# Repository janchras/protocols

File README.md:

Protocols of 4th year in HTL Kaindorf

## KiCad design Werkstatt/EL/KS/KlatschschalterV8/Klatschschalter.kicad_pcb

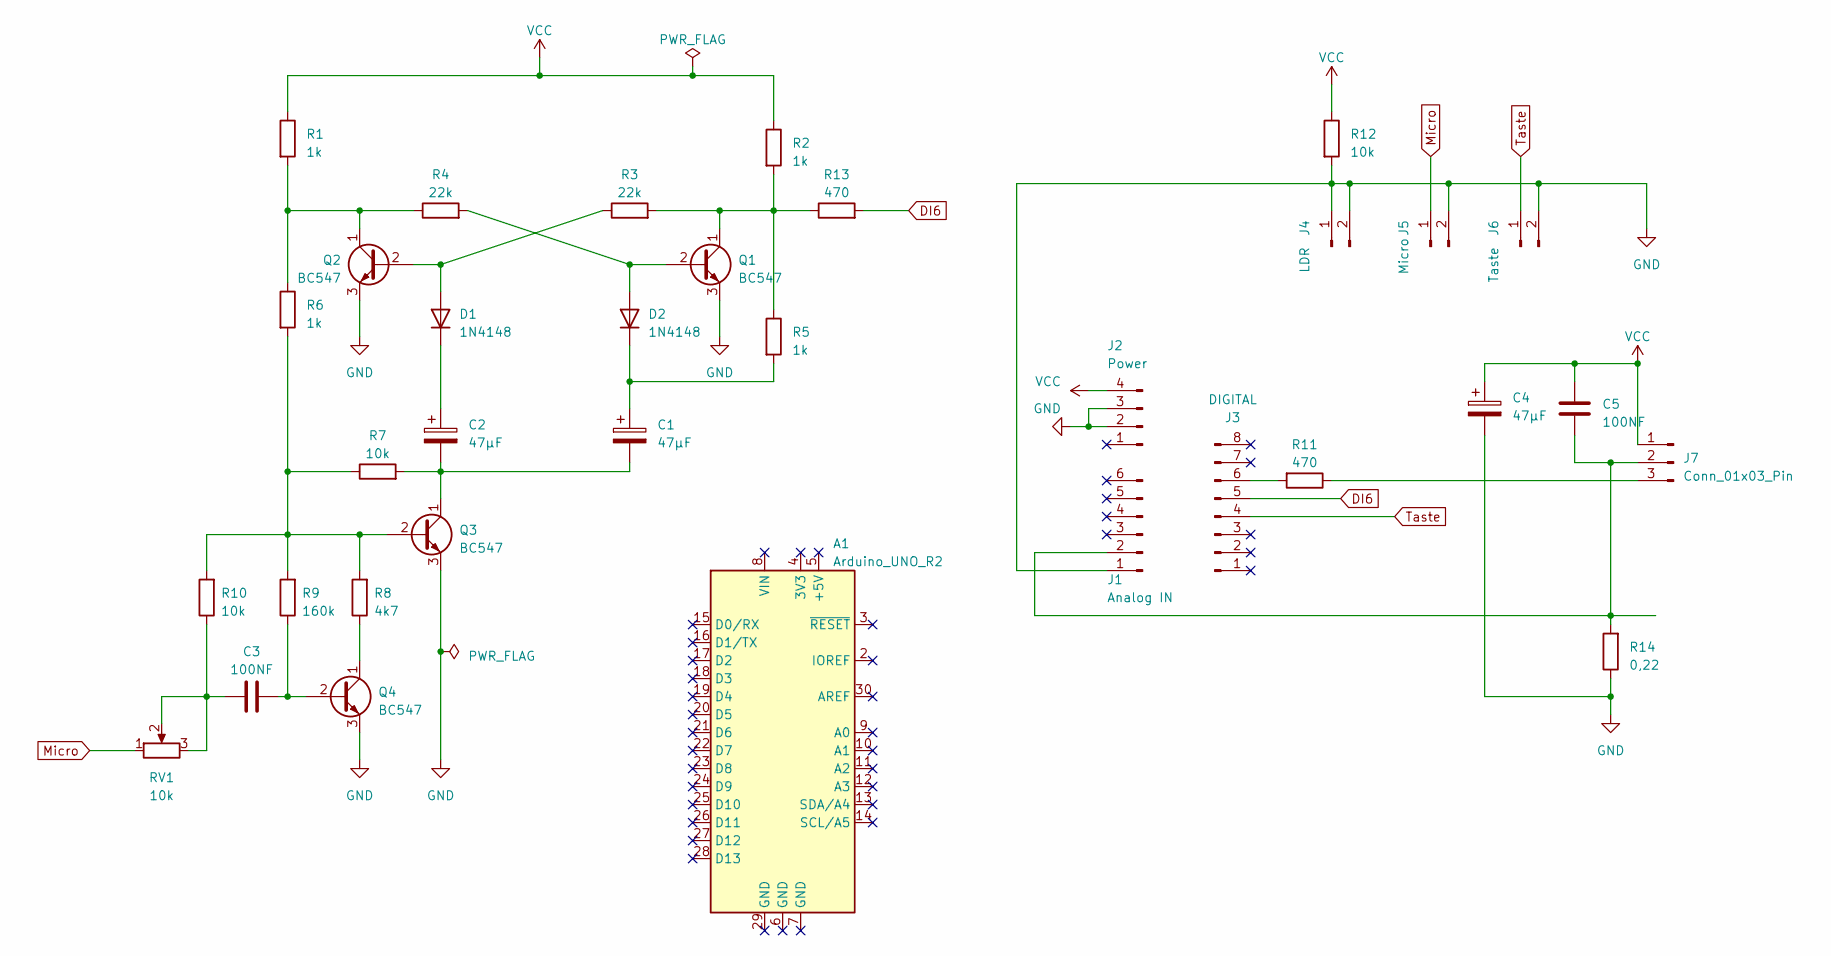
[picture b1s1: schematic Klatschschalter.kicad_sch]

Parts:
A1: Arduino_UNO_R2
C1, C2, C4: 47μF; CP_Radial_D5.0mm_P2.50mm
C3, C5: 100NF; C_Disc_D7.0mm_W2.5mm_P5.00mm
D1, D2: 1N4148; D_DO-35_SOD27_P7.62mm_Horizontal
J1: Analog IN; PinHeader_1x06_P2.54mm_Vertical
J2: Power; PinHeader_1x04_P2.54mm_Vertical
J3: DIGITAL; PinHeader_1x08_P2.54mm_Vertical
J4: LDR; PinHeader_1x02_P2.54mm_Vertical
J5: Micro; PinHeader_1x02_P2.54mm_Vertical
J6: Taste; PinHeader_1x02_P2.54mm_Vertical
J7: Conn_01x03_Pin; PinHeader_1x03_P2.54mm_Vertical
Q1, Q2, Q3, Q4: BC547; TO-92L_Inline_Wide
R1, R2, R5, R6: 1k; R_Axial_DIN0207_L6.3mm_D2.5mm_P10.16mm_Horizontal
R3, R4: 22k; R_Axial_DIN0207_L6.3mm_D2.5mm_P10.16mm_Horizontal
R7, R10, R12: 10k; R_Axial_DIN0207_L6.3mm_D2.5mm_P10.16mm_Horizontal
R8: 4k7; R_Axial_DIN0207_L6.3mm_D2.5mm_P10.16mm_Horizontal
R9: 160k; R_Axial_DIN0207_L6.3mm_D2.5mm_P10.16mm_Horizontal
R11, R13: 470; R_Axial_DIN0207_L6.3mm_D2.5mm_P10.16mm_Horizontal
R14: 0,22; R_Axial_DIN0207_L6.3mm_D2.5mm_P10.16mm_Horizontal
RV1: 10k; Potentiometer_Piher_PT-10-V10_Vertical_Hole

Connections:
DI6: J3.5, R13.2
GND: C4.2, J1.1, J2.2, J2.3, J4.1, J4.2, J5.2, J6.2, Q1.3 (E), Q2.3 (E), Q3.3 (E), Q4.3 (E), R12.2, R14.1
Micro: J5.1, RV1.1
unnamed: C3.1, R10.1, RV1.2, RV1.3
unnamed: D1.2 (A), Q2.2 (B), R3.1
unnamed: C2.1, D1.1 (K)
unnamed: D2.2 (A), Q1.2 (B), R4.2
unnamed: C1.1, D2.1 (K), R5.2
unnamed: C5.1, J1.2, J7.2, R14.2
unnamed: J3.6, R11.2
unnamed: J7.3, R11.1
unnamed: Q1.1 (C), R2.2, R3.2, R5.1, R13.1
unnamed: Q2.1 (C), R1.2, R4.1, R6.1
unnamed: Q3.2 (B), R6.2, R7.1, R8.2, R9.2, R10.2
unnamed: C1.2, C2.2, Q3.1 (C), R7.2
unnamed: C3.2, Q4.2 (B), R9.1
unnamed: Q4.1 (C), R8.1
Taste: J3.4, J6.1
VCC: C4.1, C5.2, J2.4, J7.1, R1.1, R2.1, R12.1

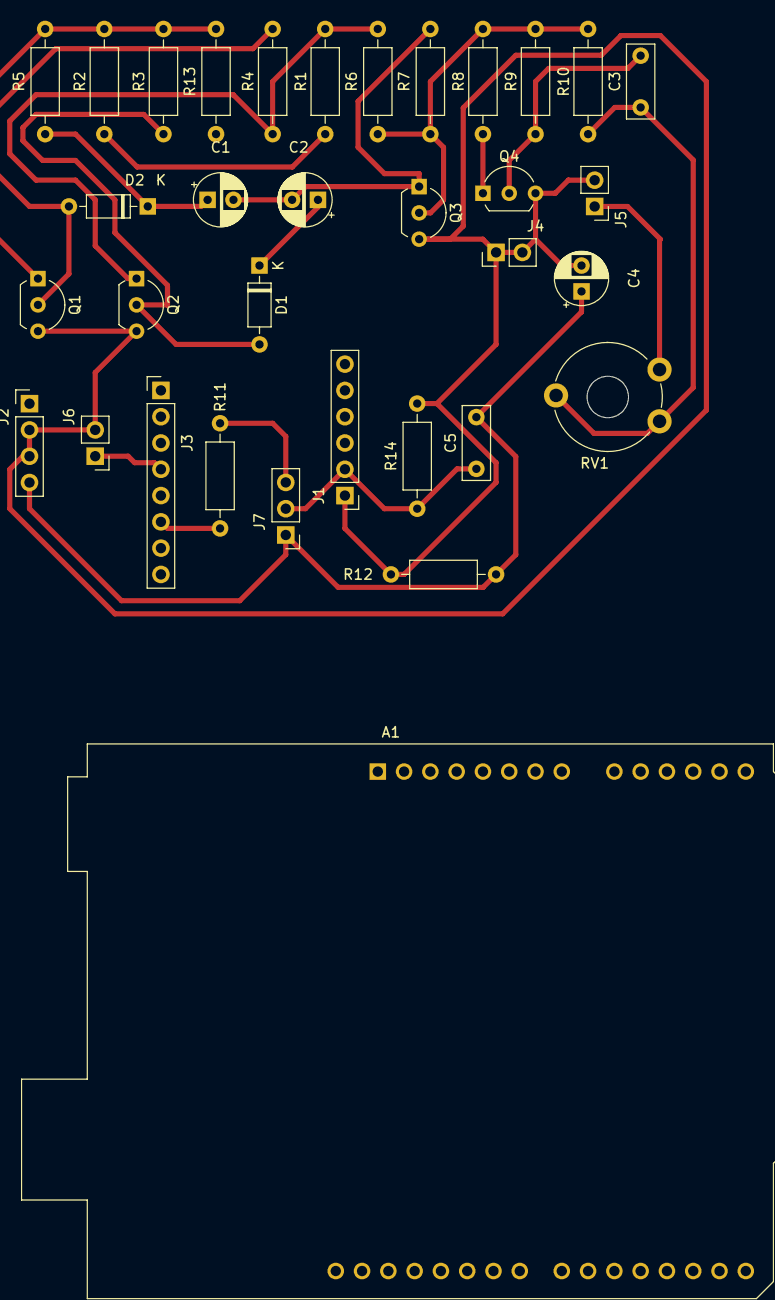
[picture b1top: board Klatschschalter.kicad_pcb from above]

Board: 2 copper layers, 34 parts (0 on the bottom side), 19 nets.

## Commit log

2024-05-16 ue12
2024-06-06 renamed .pdf
2024-06-10 added pdf folder where pdf protocols go
2024-06-11 added protocol from 4.6.24
2024-06-18 added protocol ST from 11.06
2024-07-12 added Angabe
2025-01-11 update zu 11/1/2025
